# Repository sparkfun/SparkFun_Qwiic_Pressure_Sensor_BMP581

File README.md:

SparkFun Pressure Sensor - BMP581 (Qwiic) 
=========================================

<table class="table table-hover table-striped table-bordered">
  <tr align="center">
    <td></td>
    <td></td>
  </tr>
  <tr align="center">
    <td><a href="https://www.sparkfun.com/products/20170"><i>SparkFun Pressure Sensor - BMP581 (Qwiic)</i></a></td>
    <td><a href="https://www.sparkfun.com/products/20171"><i>SparkFun Micro Pressure Sensor - BMP581 (Qwiic)</i></a></td>
  </tr>
</table>

The SparkFun Pressure Sensor - BMP581 (Qwiic) and Micro Pressure Sensor - BMP581 (Qwiic) features the BMP581 pressure sensor from Bosch Sensortec. The BMP581 boasts exceptional resolution (down to 1/64 Pa) and accuracy  and uses on-chip linearization and temperature compensation to provide true absolute data for pressure and temperature. 

The BMP581 has a wide pressure sensing range (30 to 125 kPa) with excellent accuracy across the sensing range (&plusmn; 0.5 hPa (max)) as well as output data rates up to 622 Hz. The sensor includes a configurable oversampling setting, FIFO buffer for storing up to 32 pressure samples, programmable low-pass filtering and even 6-bytes of user-programmable non-volatile memory. All of this allows you to customize the performance based on your application's requirements. Even without filtering, the BMP581 has very low noise (< 0.1Pa RMS).

Repository Contents
-------------------
* **/Documents** - Datasheet
* **/Hardware** - Eagle design files (.brd, .sch)
* **/Production** - Production panel files (.brd)

Documentation
-------------
* **[Hookup Guide](https://learn.sparkfun.com/tutorials/qwiic-pressure-sensor-bmp581-hookup-guide)** - Basic Hookup Guide for the SparkFun Pressure Sensor - BMP581 (Qwiic)
* **[BMP581 Arduino Library](https://github.com/sparkfun/SparkFun_BMP581_Arduino_Library)** - Arduino library for the BMP581 based off the Bosch API.

Product Versions
----------------
* [SEN-20170](https://www.sparkfun.com/products/20170) - Standard Size Initial Release.
* [SEN-20171](https://www.sparkfun.com/products/20171) - Micro Size Initial Release.

License Information
-------------------

This product is _**open source**_! 

Please review the LICENSE.md file for license information.

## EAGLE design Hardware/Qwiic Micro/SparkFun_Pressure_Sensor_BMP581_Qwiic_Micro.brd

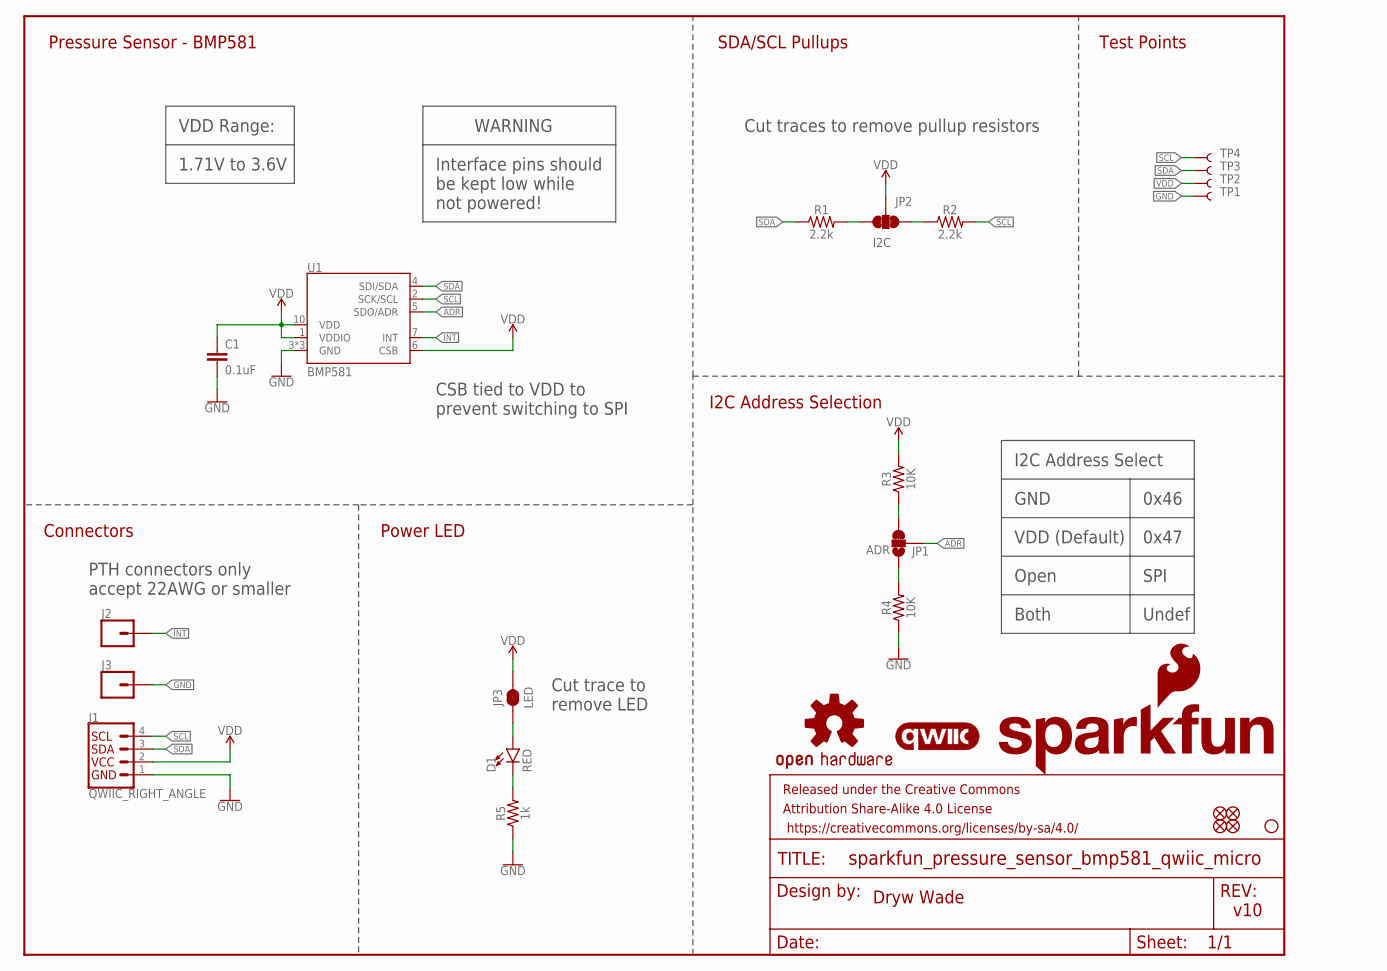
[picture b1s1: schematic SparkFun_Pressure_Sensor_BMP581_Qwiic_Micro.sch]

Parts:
C1: 0.1uF; 0402-TIGHT
D1: RED; LED-0402
FD1, FD2, FD3, FD4: FIDUCIALUFIDUCIAL; FIDUCIAL-MICRO
FRAME1: FRAME-LETTER; CREATIVE_COMMONS
H1: STAND-OFF
J1: QWIIC_RIGHT_ANGLE; JST04_1MM_RA
J2, J3: CONN_01_1MM; 1X01_1MM_NO_SILK
JP1: ADR; SMT-JUMPER_3_1-NC_TRACE_SILK
JP2: I2C; SMT-JUMPER_3_2-NC_TRACE_SILK
JP3: LED; SMT-JUMPER_2_NC_TRACE_SILK
LOGO1: OSHW-LOGOMINI; OSHW-LOGO-MINI
LOGO2: SFE_LOGO_FLAME.1_INCH; SFE_LOGO_FLAME_.1
LOGO3: QWIIC_LOGO_3MM; QWIIC_3MM
LOGO4: SFE_LOGO_NAMEBLANK; BLANK
R1, R2: 2.2k; 0402-TIGHT
R3, R4: 10K; 0402-TIGHT
R5: 1k; 0402-TIGHT
TP1, TP2, TP3, TP4: TEST-POINT3; PAD.03X.03
U1: BMP581

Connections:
ADR: JP1.2, U1.5 (SDO/ADR)
GND: C1.2, J1.1, J3.1, R4.1, R5.1, TP1.1, U1.3 (GND), U1.8 (GND), U1.9 (GND)
INT: J2.1, U1.7 (INT)
unnamed: JP1.3, R3.1
unnamed: JP1.1, R4.2
unnamed: JP2.1, R2.1
unnamed: JP2.3, R1.2
unnamed: D1.A, JP3.1
unnamed: D1.C, R5.2
SCL: J1.4, R2.2, TP4.1, U1.2 (SCK/SCL)
SDA: J1.3, R1.1, TP3.1, U1.4 (SDI/SDA)
VDD: C1.1, J1.2, JP2.2, JP3.2, R3.2, TP2.1, U1.1 (VDDIO), U1.6 (CSB), U1.10 (VDD)

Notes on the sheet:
Dryw Wade
v10
Pressure Sensor - BMP581
I2C Address Selection
I2C Address Select
GND
VDD (Default)
0x46
0x47
Open
Both
SPI
Undef
VDD Range:
1.71V to 3.6V
WARNING
Interface pins should be kept low while not powered!
Connectors
SDA/SCL Pullups
Cut traces to remove pullup resistors
Test Points
Power LED
Cut trace to remove LED
PTH connectors only accept 22AWG or smaller
CSB tied to VDD to prevent switching to SPI

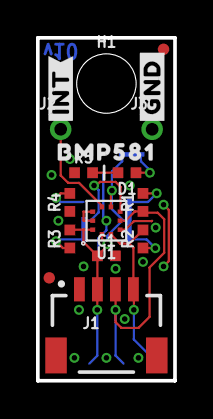
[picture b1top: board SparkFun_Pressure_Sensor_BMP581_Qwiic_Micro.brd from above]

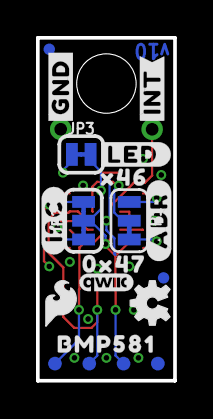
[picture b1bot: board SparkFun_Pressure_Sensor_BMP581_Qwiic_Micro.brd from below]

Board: 2 copper layers, 7.6 x 19.1 mm, 39 parts (20 on the bottom side), 12 nets.

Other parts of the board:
U$1, U$2: BMP5810
U$3: #I2C#0
U$4: #ADR#0
U$5, U$6: #GND#0
U$7, U$8: #INT#0
U$9: #LED#0
U$10: X460
U$11: 0X470

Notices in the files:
parts and their libraries:
SparkFun-Aesthetics: Licensing: Creative Commons ShareAlike 4.0 International - https://creativecommons.org/licenses/by-sa/4.0
SparkFun-Aesthetics: Released under the Creative Commons Attribution Share-Alike 4.0 License
SparkFun-Aesthetics: https://creativecommons.org/licenses/by-sa/4.0
